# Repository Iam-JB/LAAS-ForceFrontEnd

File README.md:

# LAAS-ForceFrontEnd

Electronics development to acquire and process force measurements produced by an actuator in order to achieve torque control.

Here you will find the technical review :  and the poster here : 

Files sumarry :  
      KiCAD Schematic of our own acquisition PCB  
      KiCAD PCB Routing of our own acquisition PCB  
          Code in order to flash Raspberry Pi Pico  
                  Parceur that extracts force value from an external file ('xxx.bin') and plots through MatPlotLib  
          Parceur that extracts data directly from serial port and plots through PlotJuggler

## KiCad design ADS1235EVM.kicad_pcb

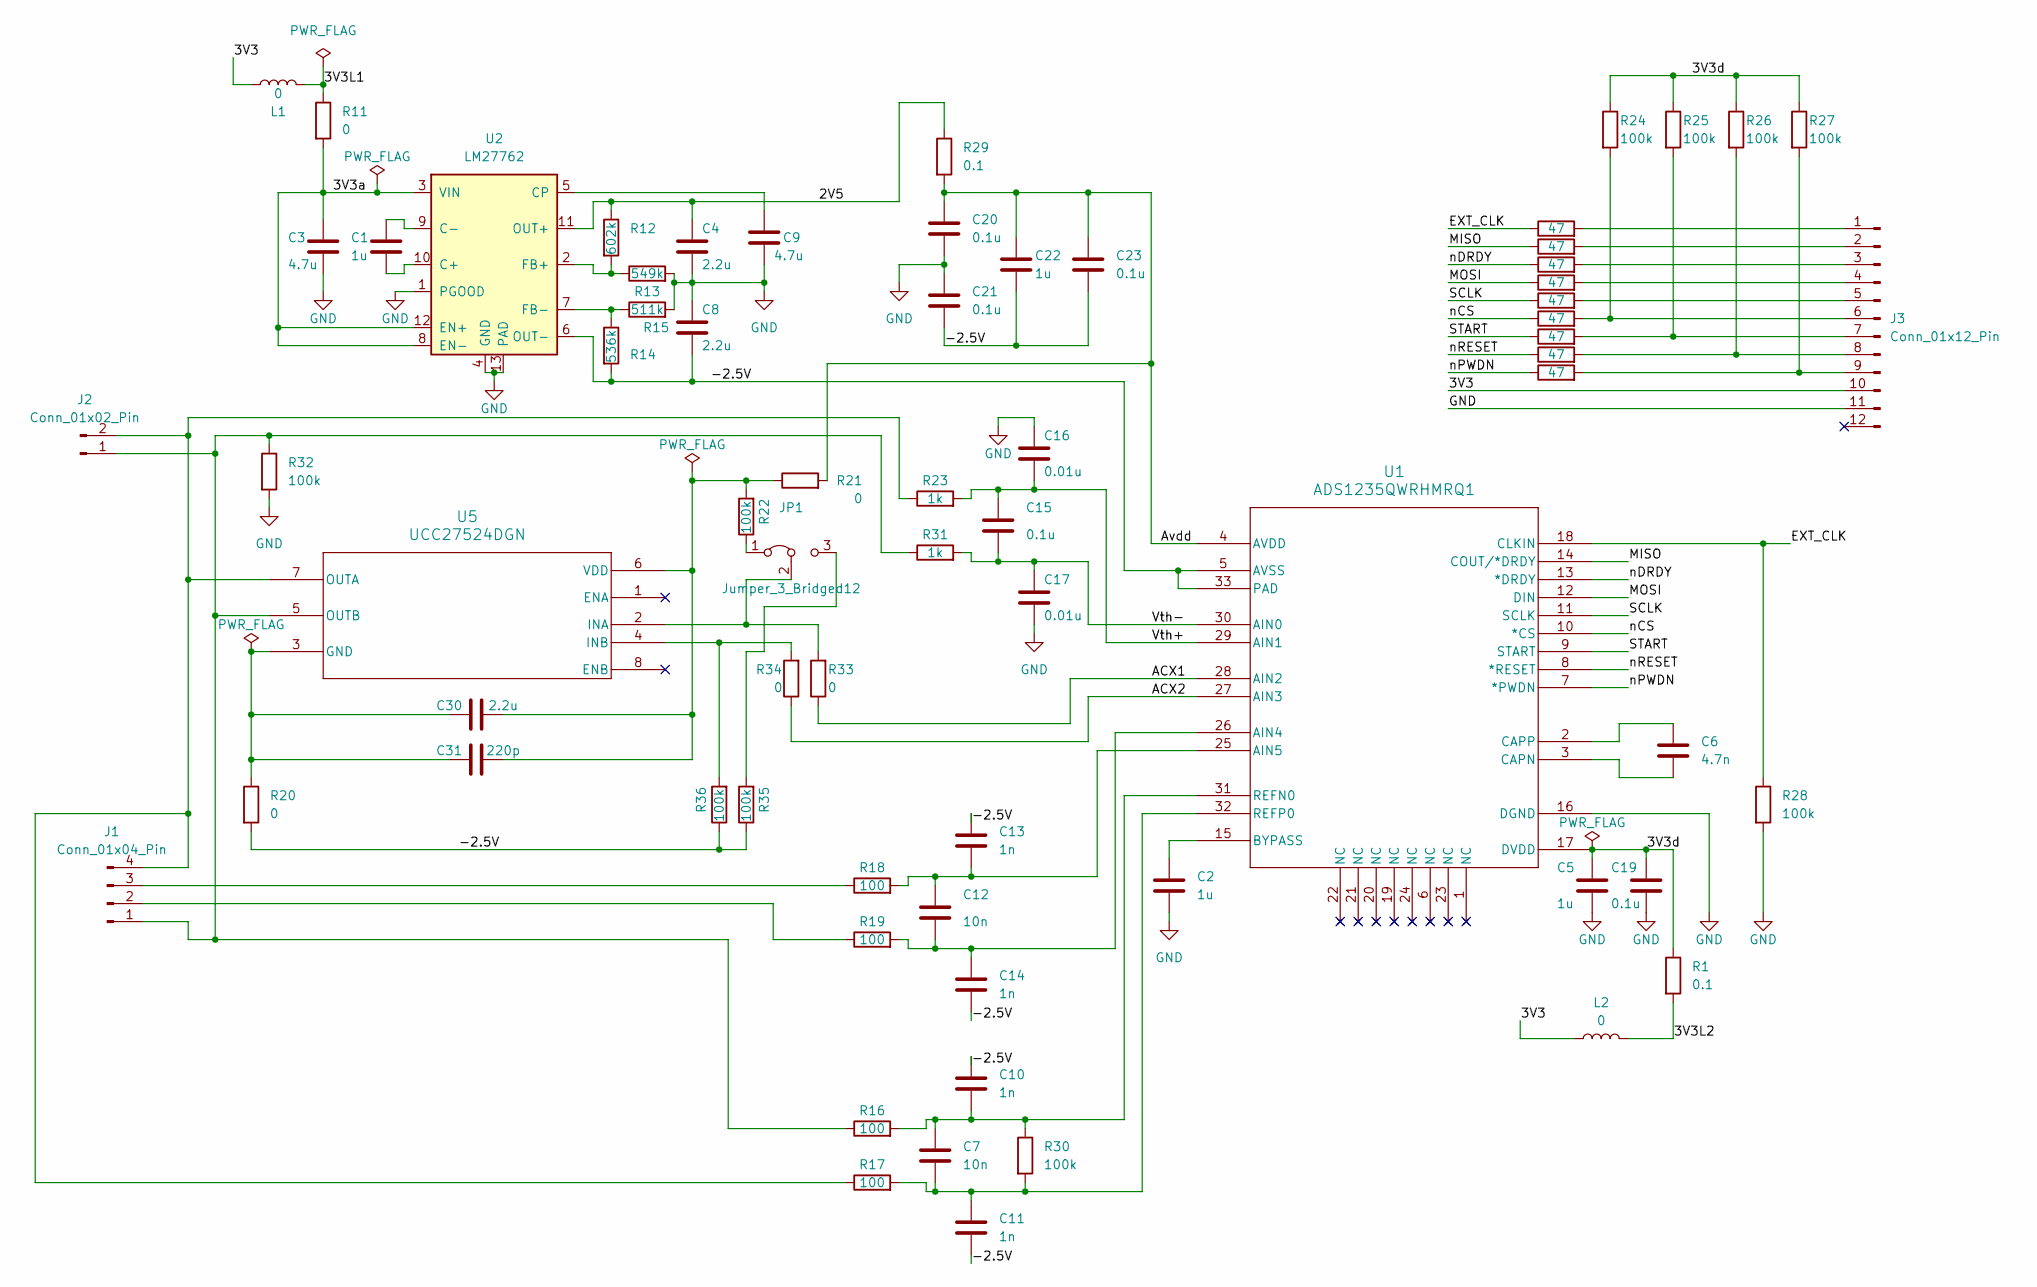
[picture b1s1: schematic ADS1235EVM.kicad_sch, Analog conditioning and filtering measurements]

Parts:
C1, C2, C5, C22: 1u; C_0402_1005Metric
C3, C9: 4.7u; C_0402_1005Metric
C4, C8, C30: 2.2u; C_0402_1005Metric
C6: 4.7n; C_0402_1005Metric
C7, C12: 10n; C_0402_1005Metric
C10, C11, C13, C14: 1n; C_0402_1005Metric
C15, C19, C20, C21, C23: 0.1u; C_0402_1005Metric
C16, C17: 0.01u; C_0402_1005Metric
C31: 220p; C_0402_1005Metric
J1: Conn_01x04_Pin; Hirose_DF13-04P-1.25DSA_1x04_P1.25mm_Vertical
J2: Conn_01x02_Pin; Hirose_DF13-02P-1.25DSA_1x02_P1.25mm_Vertical
J3: Conn_01x12_Pin; PinHeader_2x06_P2.54mm_Vertical
JP1: Jumper_3_Bridged12; SolderJumper-3_P1.3mm_Open_RoundedPad1.0x1.5mm
L1, L2: 0; L_0402_1005Metric
R1, R29: 0.1; R_0402_1005Metric
R2, R3, R4, R5, R6, R7, R8, R9, R10: 47; R_0402_1005Metric
R11, R20, R21, R33, R34: 0; R_0402_1005Metric
R12: 602k; R_0402_1005Metric
R13: 549k; R_0402_1005Metric
R14: 536k; R_0402_1005Metric
R15: 511k; R_0402_1005Metric
R16, R17, R18, R19: 100; R_0402_1005Metric
R22, R24, R25, R26, R27, R28, R30, R32, R35, R36: 100k; R_0402_1005Metric
R23, R31: 1k; R_0402_1005Metric
U1: ADS1235QWRHMRQ1; RHM0032A_VQFNP_TEX
U2: LM27762; WSON-12-1EP_3x2mm_P0.5mm_EP1x2.65_ThermalVias
U5: UCC27524DGN; DGN8

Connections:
/2V5: C4.1, R12.1, R29.1, U2.11 (OUT+)
/3V3: J3.10, L1.1, L2.1
/3V3L1: L1.2, R11.1
/3V3L2: L2.2, R1.2
/3V3a: C3.1, R11.2, U2.3 (VIN), U2.8 (EN-), U2.12 (EN+)
/3V3d: C5.1, C19.1, R1.1, R24.1, R25.1, R26.1, R27.1, U1.17 (DVDD)
/-2.5V: C8.2, C10.1, C11.2, C13.1, C14.2, C21.2, C22.2, C23.2, R14.2, R20.2, R35.1, R36.1, U1.5 (AVSS), U1.33 (PAD), U2.6 (OUT-)
/ACX1: R33.1, U1.28 (AIN2)
/ACX2: R34.1, U1.27 (AIN3)
/Avdd: C20.1, C22.1, C23.1, R21.2, R29.2, U1.4 (AVDD)
/EXT_CLK: R7.1, R28.1, U1.18 (CLKIN)
/MISO: R3.1, U1.14 (COUT/*DRDY)
/MOSI: R4.1, U1.12 (DIN)
/SCLK: R5.1, U1.11 (SCLK)
/START: R9.1, U1.9 (START)
/Vth+: C15.1, C16.2, R23.2, U1.29 (AIN1)
/Vth-: C15.2, C17.1, R31.2, U1.30 (AIN0)
/nCS: R6.1, U1.10 (*CS)
/nDRDY: R2.1, U1.13 (*DRDY)
/nPWDN: R10.1, U1.7 (*PWDN)
/nRESET: R8.1, U1.8 (*RESET)
GND: C2.2, C3.2, C4.2, C5.2, C8.1, C9.2, C16.1, C17.2, C19.2, C20.2, C21.1, J3.11, R13.2, R15.2, R28.2, R32.2, U1.16 (DGND), U2.1 (PGOOD), U2.4 (GND), U2.13 (PAD)
unnamed: J1.1, J2.1, R16.1, R31.1, R32.1, U5.5 (OUTB)
unnamed: J1.2, R19.1
unnamed: J1.3, R18.1
unnamed: J1.4, J2.2, R17.1, R23.1, U5.7 (OUTA)
unnamed: J3.1, R7.2
unnamed: J3.2, R3.2
unnamed: J3.3, R2.2
unnamed: J3.4, R4.2
unnamed: J3.5, R5.2
unnamed: J3.6, R6.2, R24.2
unnamed: J3.7, R9.2, R25.2
unnamed: J3.8, R8.2, R26.2
unnamed: J3.9, R10.2, R27.2
unnamed: JP1.1 (A), R22.1
unnamed: JP1.3 (B), R35.2
unnamed: JP1.2 (C), R33.2, U5.2 (INA)
unnamed: C12.2, C14.1, R19.2, U1.26 (AIN4)
unnamed: C12.1, C13.2, R18.2, U1.25 (AIN5)
unnamed: C2.1, U1.15 (BYPASS)
unnamed: C6.1, U1.3 (CAPN)
unnamed: C6.2, U1.2 (CAPP)
unnamed: C7.1, C10.2, R16.2, R30.1, U1.31 (REFN0)
unnamed: C7.2, C11.1, R17.2, R30.2, U1.32 (REFP0)
unnamed: C1.2, U2.10 (C+)
unnamed: C1.1, U2.9 (C-)
unnamed: C9.1, U2.5 (CP)
unnamed: R12.2, R13.1, U2.2 (FB+)
unnamed: R14.1, R15.1, U2.7 (FB-)
unnamed: C30.1, C31.1, R20.1, U5.3 (GND)
unnamed: R34.2, R36.2, U5.4 (INB)
unnamed: C30.2, C31.2, R21.1, R22.2, U5.6 (VDD)

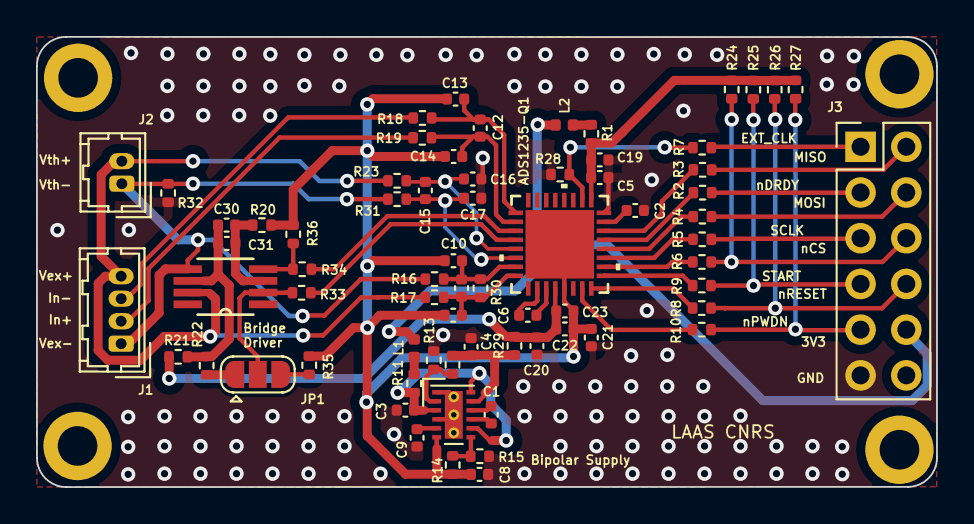
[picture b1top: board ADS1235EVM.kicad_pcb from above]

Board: 2 copper layers, 50.0 x 25.0 mm, 69 parts (0 on the bottom side), 53 nets.

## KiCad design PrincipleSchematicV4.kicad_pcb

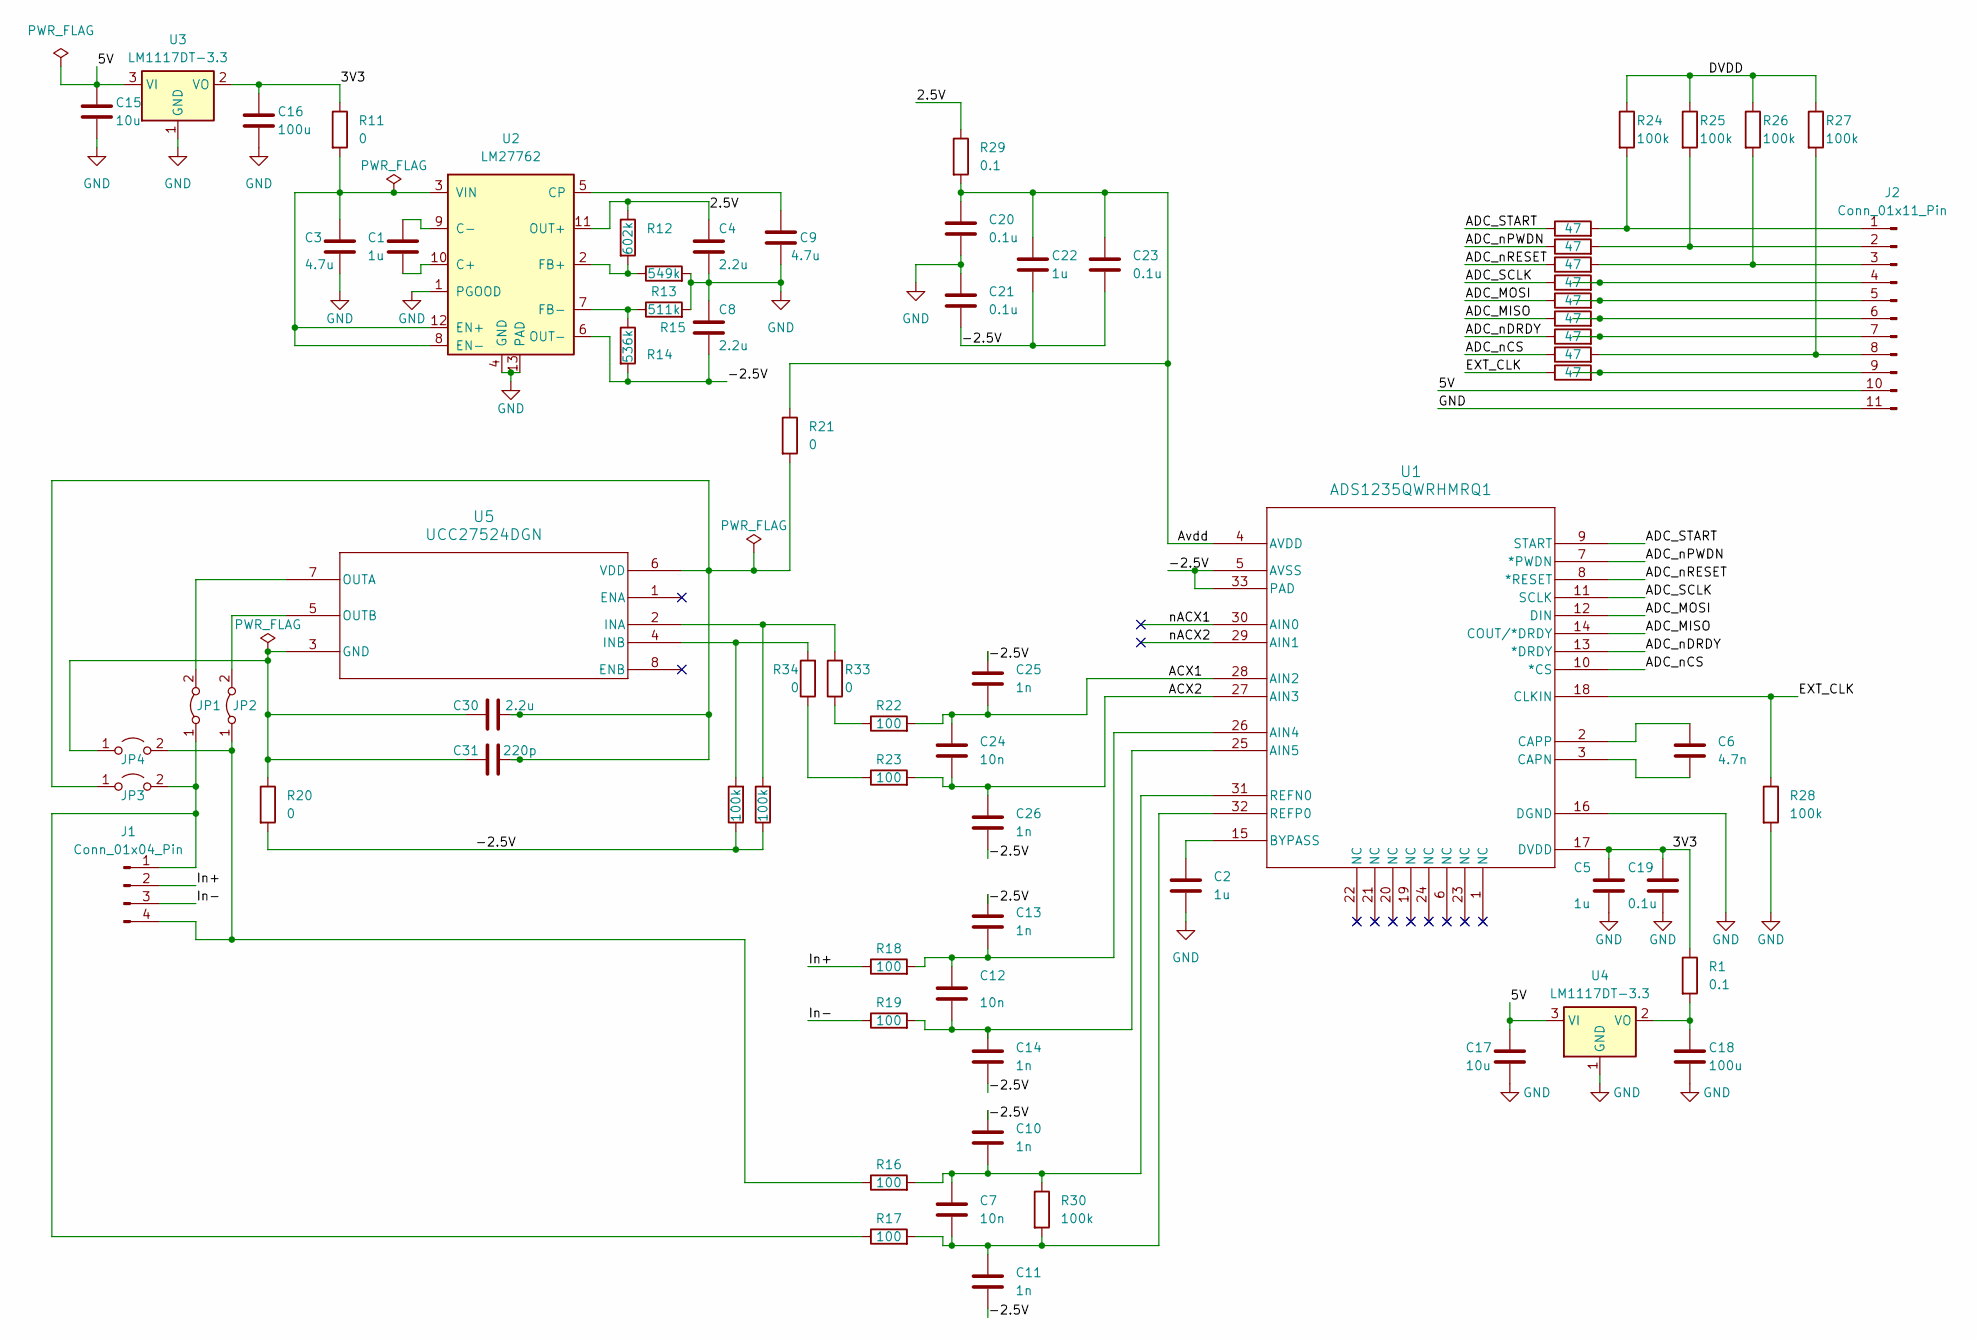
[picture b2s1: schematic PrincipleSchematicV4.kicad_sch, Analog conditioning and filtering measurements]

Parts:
C1, C2, C5, C22: 1u
C3, C9: 4.7u
C4, C8, C30: 2.2u
C6: 4.7n
C7, C12, C24: 10n
C10, C11, C13, C14, C25, C26: 1n
C15, C17: 10u
C16, C18: 100u
C19, C20, C21, C23: 0.1u
C31: 220p
J1: Conn_01x04_Pin
J2: Conn_01x11_Pin
JP1, JP2: Jumper_2_Bridged
JP3, JP4: Jumper_2_Open
R1, R29: 0.1
R2, R3, R4, R5, R6, R7, R8, R9, R10: 47
R11, R20, R21, R33, R34: 0
R12: 602k
R13: 549k
R14: 536k
R15: 511k
R16, R17, R18, R19, R22, R23: 100
R24, R25, R26, R27, R28, R30, R35, R36: 100k
U1: ADS1235QWRHMRQ1; RHM0032A_VQFNP_TEX
U2: LM27762; WSON-12-1EP_3x2mm_P0.5mm_EP1x2.65_ThermalVias
U3, U4: LM1117DT-3.3; TO-252-3_TabPin2
U5: UCC27524DGN; DGN8

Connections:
/2.5V: C4.1, R12.1, R29.1, U2.11 (OUT+)
/3V3: C5.1, C16.1, C19.1, R1.1, R11.1, U1.17 (DVDD), U3.2 (VO)
/5V: C15.1, C17.1, J2.10, U3.3 (VI), U4.3 (VI); also elsewhere on the board
/-2.5V: C8.2, C10.1, C11.2, C13.1, C14.2, C21.2, C22.2, C23.2, C25.1, C26.2, R14.2, R20.2, R35.1, R36.1, U1.5 (AVSS), U1.33 (PAD), U2.6 (OUT-)
/ACX1: C24.1, C25.2, R22.2, U1.28 (AIN2)
/ACX2: C24.2, C26.1, R23.2, U1.27 (AIN3)
/ADC_MISO: R6.1, U1.14 (COUT/*DRDY)
/ADC_MOSI: R5.1, U1.12 (DIN)
/ADC_SCLK: R4.1, U1.11 (SCLK)
/ADC_START: R7.1, U1.9 (START)
/ADC_nCS: R8.1, U1.10 (*CS)
/ADC_nDRDY: R9.1, U1.13 (*DRDY)
/ADC_nPWDN: R3.1, U1.7 (*PWDN)
/ADC_nRESET: R2.1, U1.8 (*RESET)
/Avdd: C20.1, C22.1, C23.1, R21.1, R29.2, U1.4 (AVDD)
/DVDD: R24.1, R25.1, R26.1, R27.1
/EXT_CLK: R10.1, R28.1, U1.18 (CLKIN)
/In+: J1.2, R18.1
/In-: J1.3, R19.1
/nACX1: U1.30 (AIN0)
/nACX2: U1.29 (AIN1)
GND: C2.2, C3.2, C4.2, C5.2, C8.1, C9.2, C15.2, C16.2, C17.2, C18.2, C19.2, C20.2, C21.1, R13.2, R15.2, R28.2, U1.16 (DGND), U2.1 (PGOOD), U2.4 (GND), U2.13 (PAD), U3.1 (GND), U4.1 (GND); also elsewhere on the board
unnamed: J1.1, JP1.1 (A), JP3.2 (B), R17.1
unnamed: J1.4, JP2.1 (A), JP4.2 (B), R16.1
unnamed: J2.1, R7.2, R24.2
unnamed: J2.2, R3.2, R25.2
unnamed: J2.3, R2.2, R26.2
unnamed: J2.4, R4.2
unnamed: J2.5, R5.2
unnamed: J2.6, R6.2
unnamed: J2.7, R9.2
unnamed: J2.8, R8.2, R27.2
unnamed: J2.9, R10.2
unnamed: JP1.2 (B), U5.7 (OUTA)
unnamed: JP2.2 (B), U5.5 (OUTB)
unnamed: C30.2, C31.2, JP3.1 (A), R21.2, U5.6 (VDD)
unnamed: C30.1, C31.1, JP4.1 (A), R20.1, U5.3 (GND)
unnamed: R22.1, R33.1
unnamed: R23.1, R34.1
unnamed: C12.1, C13.2, R18.2, U1.26 (AIN4)
unnamed: C12.2, C14.1, R19.2, U1.25 (AIN5)
unnamed: C2.1, U1.15 (BYPASS)
unnamed: C6.1, U1.3 (CAPN)
unnamed: C6.2, U1.2 (CAPP)
unnamed: C7.1, C10.2, R16.2, R30.1, U1.31 (REFN0)
unnamed: C7.2, C11.1, R17.2, R30.2, U1.32 (REFP0)
unnamed: C1.2, U2.10 (C+)
unnamed: C1.1, U2.9 (C-)
unnamed: C9.1, U2.5 (CP)
unnamed: C3.1, R11.2, U2.3 (VIN), U2.8 (EN-), U2.12 (EN+)
unnamed: R12.2, R13.1, U2.2 (FB+)
unnamed: R14.1, R15.1, U2.7 (FB-)
unnamed: C18.1, R1.2, U4.2 (VO)
unnamed: R33.2, R35.2, U5.2 (INA)
unnamed: R34.2, R36.2, U5.4 (INB)

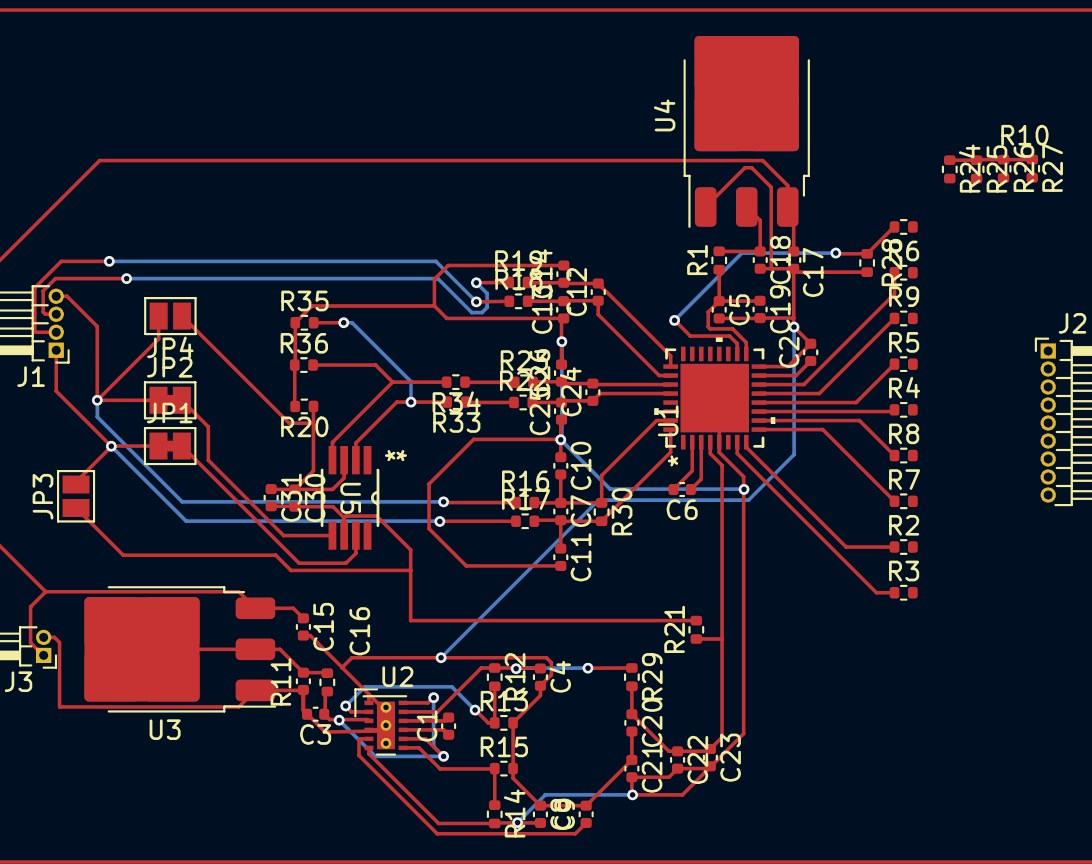
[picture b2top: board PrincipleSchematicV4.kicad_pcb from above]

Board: 2 copper layers, 74 parts (0 on the bottom side), 53 nets.

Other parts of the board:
J3: Conn_01x02_Pin; PinHeader_1x02_P1.00mm_Horizontal

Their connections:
/5V: J3.1; also elsewhere on the board
GND: J3.2; also elsewhere on the board

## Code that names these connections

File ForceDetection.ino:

#include <stdio.h>
#include <SPI.h>

// Jean-Baptiste CAZAUX - Tuesday 16 July
// https://github.com/Iam-JB/LAAS-ForceFrontEnd

// GPIOs DEFINITION
const int nCS = 17;
const int START = 20;
const int nDRDY = 21;
const int nPWDN = 26;
const int nRESET = 22;

// Buffers
const int SYNC = 0x31;
uint16_t counter = 0x0000;      // Counter 16 bits
uint8_t tabToBeSendUART[6];

void initPiPico() {
    // Initialize GPIO pins
    pinMode(nCS, OUTPUT);
    pinMode(START, OUTPUT);
    pinMode(nRESET, OUTPUT);
    pinMode(nPWDN, OUTPUT);
    pinMode(nDRDY, INPUT);

    // Initialize SPI
    SPI.begin();
    SPI.beginTransaction(SPISettings(4000000,MSBFIRST,SPI_MODE1));
}

// READ ADS1235Q1's REGISTERS
uint8_t readRegister(uint8_t address) {
    uint8_t command = 0x20 + (address & 0x1F); // RREG is a 0x20 + rrh, where rrh is a 5-bit register
    digitalWrite(nCS, LOW);
    SPI.transfer(command);
    SPI.transfer(0xFF);
    uint8_t value = SPI.transfer(0x00);
    digitalWrite(nCS, HIGH);
    return value;
}

// WRITE ADS1235Q1's REGISTERS
void writeRegister(uint8_t address, uint8_t value) {
    digitalWrite(nCS, LOW);
    uint8_t command = 0x40 + (address & 0x1F); // WREG is a 0x40 + rrh, where rrh is a 5-bit register
    SPI.transfer(command);
    SPI.transfer(value);
    digitalWrite(nCS, HIGH);
}

void setupMain() {
    // INIT
    Serial.begin();   // No need to specify serial speed for Pi Pico due to virtual UART
    while(!Serial);
    initPiPico();

    digitalWrite(nCS, HIGH);
    digitalWrite(nRESET, HIGH);
    digitalWrite(nPWDN, HIGH);
    digitalWrite(START, LOW);

    // DC-EXCITATION CONFIGURATION
    uint8_t addressEXC = 0b00011;
    uint8_t valueDC = 0b00001001;  // DC-EXCITATION and conversion start delay = 1.16ms (cf. datasheet)
    writeRegister(addressEXC, valueDC);

    // DATA RATE CONFIGURATION
    uint8_t addressDR = 0b00010;
//    uint8_t valueDR = 0b01100011;  // 7200 SPS & sinc1 (-3dB cutoff frequency at 2300Hz)
//    uint8_t valueDR = 0b01100011;  // 7200 SPS & sinc2 (-3dB cutoff frequency at 1960Hz)
//    uint8_t valueDR = 0b01100011;  // 7200 SPS & sinc3 (-3dB cutoff frequency at 1740Hz)
    uint8_t valueDR = 0b01100011;  // 7200 SPS & sinc4 (-3dB cutoff frequency at 1580Hz)
    writeRegister(addressDR, valueDR);

    // PGA CONFIGURATION
    uint8_t addressPGA = 0b10000;
    uint8_t valuePGA = 0b10000111;  // Gain of 128
    writeRegister(addressPGA, valuePGA);

    // INPUT MULTIPLEXER CONFIGURATION
    uint8_t addressMUX = 0b10001;
    uint8_t valueMUX = 0b01111000;  // AIN4(+) and AIN5(-)
    writeRegister(addressMUX, valueMUX);

    // REFERENCE CONFIGURATION
    uint8_t addressREF = 0b00110;
    uint8_t valueREF = 0b00001010;
    writeRegister(addressREF, valueREF);

    // USER CALIBRATION
       // OFCAL
    // writeRegister(0x07, 0x00); // Follow the user calibration procedure (cf. datasheet)
    // writeRegister(0x08, 0x00);
    // writeRegister(0x09, 0x00);
    writeRegister(0x07, 0x7D); // Follow the user calibration procedure (cf. datasheet)
    writeRegister(0x08, 0x27);
    writeRegister(0x09, 0x04);

      // FSCAL
    writeRegister(0x0A, 0x00); // Follow the user calibration procedure (cf. datasheet)
    writeRegister(0x0B, 0x00);
    writeRegister(0x0C, 0x40);
  //  writeRegister(0x0A, 0xCC);
  //  writeRegister(0x0B, 0xCC);
  //  writeRegister(0x0C, 0x3C);
}


void myCallback() {
    uint32_t ADC_VALUE = 0;
    
    digitalWrite(nCS, LOW);
    SPI.transfer(0x12);
    SPI.transfer(0xFF);
    uint8_t MSB = SPI.transfer(0x00);
    uint8_t MIDSB = SPI.transfer(0x00);
    uint8_t LSB = SPI.transfer(0x00);
    digitalWrite(nCS, HIGH);

    int data[3] = {MSB,MIDSB,LSB};
    for (int i = 0 ; i <= 2 ; i++){
      ADC_VALUE = (ADC_VALUE << 8) | data[i];
    }
    uint32_t ADC_VALUE_DATA = ADC_VALUE & 0x7FFFFF ;
    uint32_t ADC_VALUE_SIGN = (ADC_VALUE & 0x800000) >> 23 ;

    // FORMATING AS SYNC | COUNTER | FORCE_VALUE
    counter++;
    uint8_t MSBcounter = (counter & 0xFF00) >> 8 ;
    uint8_t LSBcounter = counter & 0x00FF ;
    
    tabToBeSendUART[0] = SYNC ;
    tabToBeSendUART[1] = MSBcounter ;
    tabToBeSendUART[2] = LSBcounter ;
    tabToBeSendUART[3] = MSB ;
    tabToBeSendUART[4] = MIDSB ;
    tabToBeSendUART[5] = LSB ;

    Serial.write(tabToBeSendUART,6);
    Serial.flush();

    if (counter >= 0xFFFF) { // Not really needed here as counter is defined as a uint16_t
      counter = 0x0000;
    }

}

void setup() {
    setupMain();
    digitalWrite(START, HIGH); // Start conversion acquisitions
}

void loop() {
  while (1) {
    while(!digitalRead(nDRDY));
    while(digitalRead(nDRDY));
    myCallback();
  }
}

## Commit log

2024-06-19 Schematics - All components included
2024-06-19 Schematics - Add of jumpers to handle AC or DC excitation
2024-06-21 Double Side Routing - First version
2024-06-21 Double Side Routing - Second version
    It is a more compact PCB with the add of a bottom ground surface
2024-06-24 Project - Both the schematic and routing files included
2024-06-24 Add schematic & routing files
2024-06-24 Routing - Add of 2 ferrites bead for power
2024-06-25 Routing - Tie unused analog inputs to Avdd
2024-06-25 Routing - Components placement correction + DRC OK
2024-06-25 Add of .kicad_pro file
2024-06-25 Schematic - Jumpers removed + ERC OK
2024-06-25 PCB - Add of net names
2024-06-25 PCB - Correction net names
2024-06-25 PCB - Add of components name
2024-06-25 PCB - Change of the ±Vref track size
2024-06-26 PCB - Add of 2 jumpers to handle AC & DC excitation
2024-06-26 Schematic - Add of 2 jumpers to handle AC & DC excitation
2024-06-28 PCB - Components placement optimisation & add of GND vias
2024-07-01 Association Schematic & PCB
2024-07-01 Add Arduino file for SPI
2024-07-03 Arduino - First functional version
2024-07-03 Arduino - Correction of WREG and RREG bytes
2024-07-04 Add of 2.54mm SPI connector & open jumper
2024-07-05 Arduino - Delay deleted
2024-07-08 Arduino - Wait for serial connexion
2024-07-10 Arduino - Implementation of DMA and IT
2024-07-12 Arduino DMA - Update file
2024-07-17 RPi - Add python file
2024-07-18 RPi - Functional version with IT
2024-07-22 RPi - Use of DMA
    Run the main .py script as root in order to have access to all peripherals
2024-07-23 RPi - External data visualisation with PlotJuggler
2024-07-24 RPi - Increase speed data visualisation on PlotJuggler
2024-07-24 RPi - Add of explicit comments
2024-07-24 RPi - Increase data speed visualisation
2024-07-24 RPi - Calibration in Newtons
    weight : 100g <-> adc code : 3150
2024-07-24 RPi - Noise RMS calculation
2024-07-25 RPi - Add of CLK divider 256
2024-07-29 RPi - Add of ADC internal temperature calculation
2024-08-05 KiCAD - Change ferrite net names
2024-08-05 RPi - Correction of internal temperature measurement
2024-08-08 KiCAD - Add of load cell measurement
2024-08-08 KiCAD - Adjustment of track width
2024-09-09 ESP32 - Conversion & Extraction values
2024-09-09 ESP32 - Comments modifications
2024-09-09 Pi Pico - Correction of counter bugs
2024-09-10 Pi Pico - Calibration modifications
2024-09-10 Pi Pico - Add of counter tracking functionality
2024-09-11 Pi Pico - Correction of calibration procedure
2024-09-11 Pi Pico - Take into account A2 complementary in the parseur
2024-09-13 Pi Pico - Delay deleted
2024-09-13 Pi Pico - Real-Time data extraction from serial
2024-09-18 Creation of README.md for Talos_Experimentations folder
2024-09-18 TALOS - Experimentations results
2024-09-19 Add TechnicalReview.pdf
2024-09-19 Add link to TechnicalReview.pdf
2024-09-19 Pi Pico - Functional version & Code well commented
2024-09-19 Explicit files summary in README.md
2024-09-19 Better visualisation in README.md
2024-09-19 Add of a summary poster
2024-09-19 Add the final poster in README.md
2024-09-19 Pi Pico - Add of FFT plot
2024-09-19 Pi Pico - Print deleted
